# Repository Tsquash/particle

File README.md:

# particle: A Particulate Matter Sensor

particle is an ESP32-C6-based particulate matter sensor. It measures PM1.0,
PM2.5, and PM10, displays the latest measurements locally via an e-paper display, and can send them to
a paired [AQM](https://github.com/Tsquash/AirQualityMonitor) (air quality monitor) over Bluetooth Low Energy (BLE).
The AQM is the Matter-connected device. This device acts as its PM sensor
peripheral and does not commission itself as a separate Matter device.

## Hardware

- **MCU:** Seeed Studio XIAO ESP32-C6
- **Particulate sensor:** DFRobot Fermion BMV080, connected over SPI and driven with the
  SparkFun BMV080 Arduino library
- **Display:** 2.13", 250 x 122 pixel monochrome e-paper display using the
  GDEY0213B74 panel/SSD1680 driver, driven with GxEPD2 and Adafruit GFX
- **PCB** Custom particle PCB, can be found in /KICAD directory

## Operating modes

### Standalone / Normal Operation

The PM sensor starts collecting data even when no AQM is available. It polls
the BMV080 for new output approximately every 500 ms and forms one-minute
averages. Measurements that are obstructed or outside the valid range are
not included in the average. When all samples in an interval indicate obstruction,
the display shows an obstructed status on the screen instead of a numerical reading.

Standalone operation does not require BLE or a network connection. The first
boot makes one automatic attempt to pair with an AQM; the attempt ends after
2 minutes have elapsed, then the device runs standalone until pairing is explicitly
requested again with the pairing button or a factory reset.

Note! Device takes a full minute from seeing the **particle**, **Pairing Successful**,
or **Pairing Timed Out** screen to transition into displaying values on the EPD. This
is due to the sensor having an initialization period.

### Linked to an AQM

The PM sensor pairs with the companion Matter AQM over BLE. The AQM supplies
the measurement schedule and its RTC time; the PM sensor sends its one-minute
PM averages to the AQM when a BLE connection and notification subscription
are available. The AQM can then use the readings in its air-quality matter
cluster data. The PM sensor continues to take and display local readings if
the AQM is temporarily disconnected.

Pairing is initiated automatically on the first boot. Put the AQM into its
corresponding PM-pairing mode while the PM sensor displays its pairing screen.
The pairing window lasts up to 120 seconds. On success, the peer is saved in
non-volatile storage and the PM sensor will try to reconnect to that AQM on
subsequent boots. If pairing times out, the PM sensor continues in standalone
mode; hold the pairing button for one second during a later boot to try again.

## Buttons

Both buttons are checked at boot. Hold the pairing button
for at least one second to enter AQM pairing mode. Hold the 
factory reset for at least one second, then release, to factory reset.

| Button | Location | GPIO | Action |
| --- | --- |---: | --- |
| AQM pair | Closest to back opening | 0 | Force a new pairing attempt, replacing the previously saved AQM peer |
| Factory reset | Further from back opening | 1 | Erase non-volatile storage, including the saved pairing state, and restart |

## Build, upload, and serial output

Install [PlatformIO](https://platformio.org/) and the Espressif platform
dependencies, connect the XIAO ESP32-C6, then run these commands from the
project directory:

```sh
pio run -e esp32c6
pio run -e esp32c6 -t upload
pio device monitor -b 115200
```

The PlatformIO environment is defined in [`platformio.ini`](platformio.ini).
The project uses the Arduino and ESP-IDF frameworks and is configured for the
`seeed_xiao_esp32c6` board. Serial diagnostics run at 115200 baud. Upload port
selection may need to be configured for the host computer.

## Project layout

```text
main/                  Firmware source, display assets, and project component config
  font/                Embedded Adafruit GFX fonts
lib/                   Project-local libraries (including modified GxEPD2 and BMV080 libs)
managed_components/    ESP-IDF managed components
KICAD/                 PCB and schematic design files
2D/                    Drawings
3D/                    Board, component, and enclosure models
UI/                    Display/UI mockups and PCB graphics
.vscode/               VS Code project configuration
platformio.ini         PlatformIO build environment
sdkconfig.defaults.*   ESP-IDF default configuration for the target
huge_app.csv           ESP-IDF flash partition table
dependencies.lock      Locked ESP-IDF component dependencies
```

The primary firmware files are:

- [`main/main.cpp`](main/main.cpp): boot behavior, button handling, sensor
  sampling, averaging, and the main loop
- [`main/sensor.cpp`](main/sensor.cpp): BMV080 initialization and reading
  validation
- [`main/screen.cpp`](main/screen.cpp): e-paper initialization, measurement
  display, and status screens
- [`main/pm_link.cpp`](main/pm_link.cpp): BLE pairing, reconnection, timing,
  and PM-reading transfer
- [`main/pm_protocol.h`](main/pm_protocol.h): BLE data structures shared with
  the companion AQM project

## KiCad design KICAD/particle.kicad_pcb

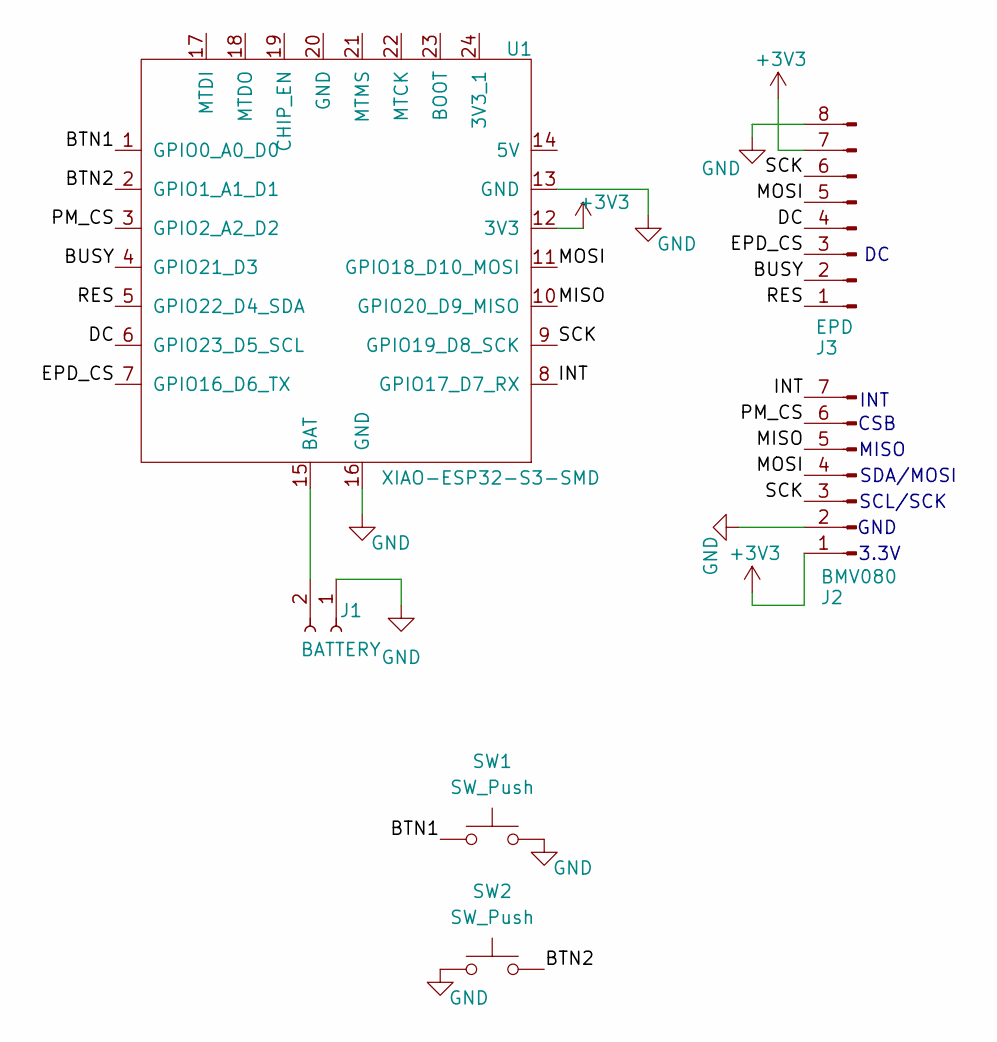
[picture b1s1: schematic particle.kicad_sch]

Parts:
J1: BATTERY; PinHeader_1x02_P2.54mm_Vertical
J2: BMV080; PinHeader_1x07_P2.54mm_Vertical
J3: EPD; PinHeader_2x04_P2.54mm_Vertical
SW1, SW2: SW_Push; SW_BUTT-2
U1: XIAO-ESP32-S3-SMD; XIAO-ESP32C6-SMD

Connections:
+3V3: J2.1, J3.7, U1.12 (3V3)
/BTN1: SW1.1, U1.1 (GPIO0_A0_D0)
/BTN2: SW2.2, U1.2 (GPIO1_A1_D1)
/BUSY: J3.2, U1.4 (GPIO21_D3)
/DC: J3.4, U1.6 (GPIO23_D5_SCL)
/EPD_CS: J3.3, U1.7 (GPIO16_D6_TX)
/INT: J2.7, U1.8 (GPIO17_D7_RX)
/MISO: J2.5, U1.10 (GPIO20_D9_MISO)
/MOSI: J2.4, J3.5, U1.11 (GPIO18_D10_MOSI)
/PM_CS: J2.6, U1.3 (GPIO2_A2_D2)
/RES: J3.1, U1.5 (GPIO22_D4_SDA)
/SCK: J2.3, J3.6, U1.9 (GPIO19_D8_SCK)
GND: J1.1, J2.2, J3.8, SW1.2, SW2.1, U1.13 (GND), U1.16 (GND)
unnamed: J1.2, U1.15 (BAT)

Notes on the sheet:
MISO
SDA/MOSI
3.3V
SCL/SCK
INT
CSB
GND

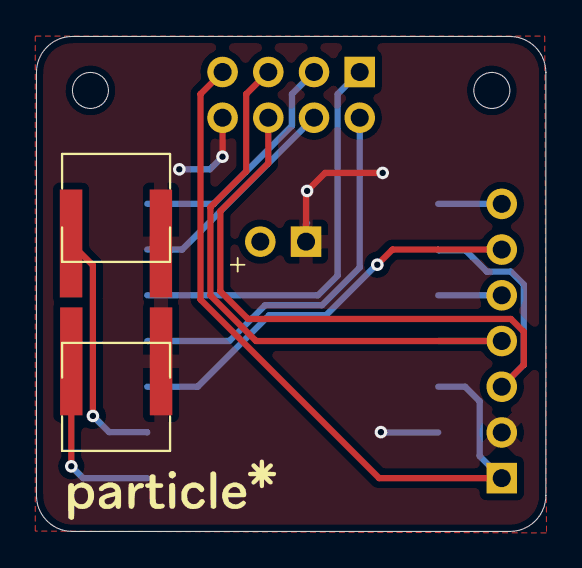
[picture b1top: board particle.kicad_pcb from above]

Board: 2 copper layers, 28.3 x 27.5 mm, 6 parts (1 on the bottom side), 14 nets.
